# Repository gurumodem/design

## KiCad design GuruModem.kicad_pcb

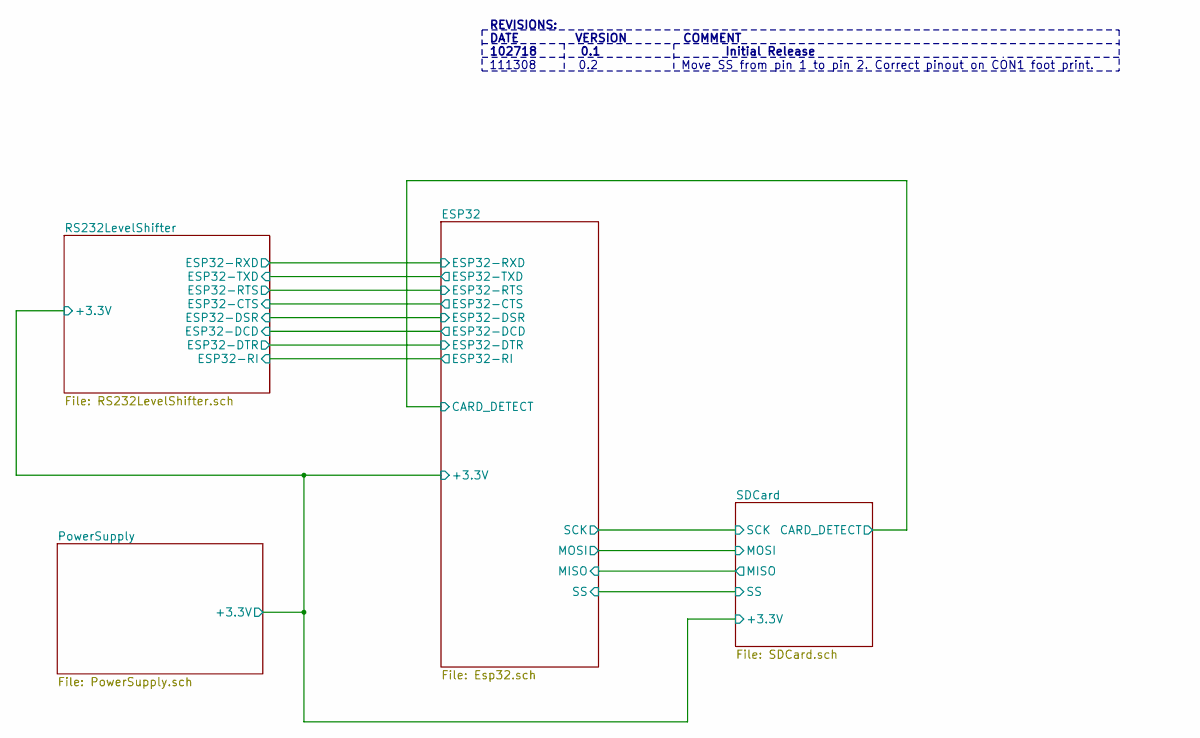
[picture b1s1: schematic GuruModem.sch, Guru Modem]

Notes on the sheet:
REVISIONS: DATE VERSION COMMENT 102718 0.1 Initial Release
111308
0.2
Move SS from pin 1 to pin 2. Correct pinout on CON1 foot print.

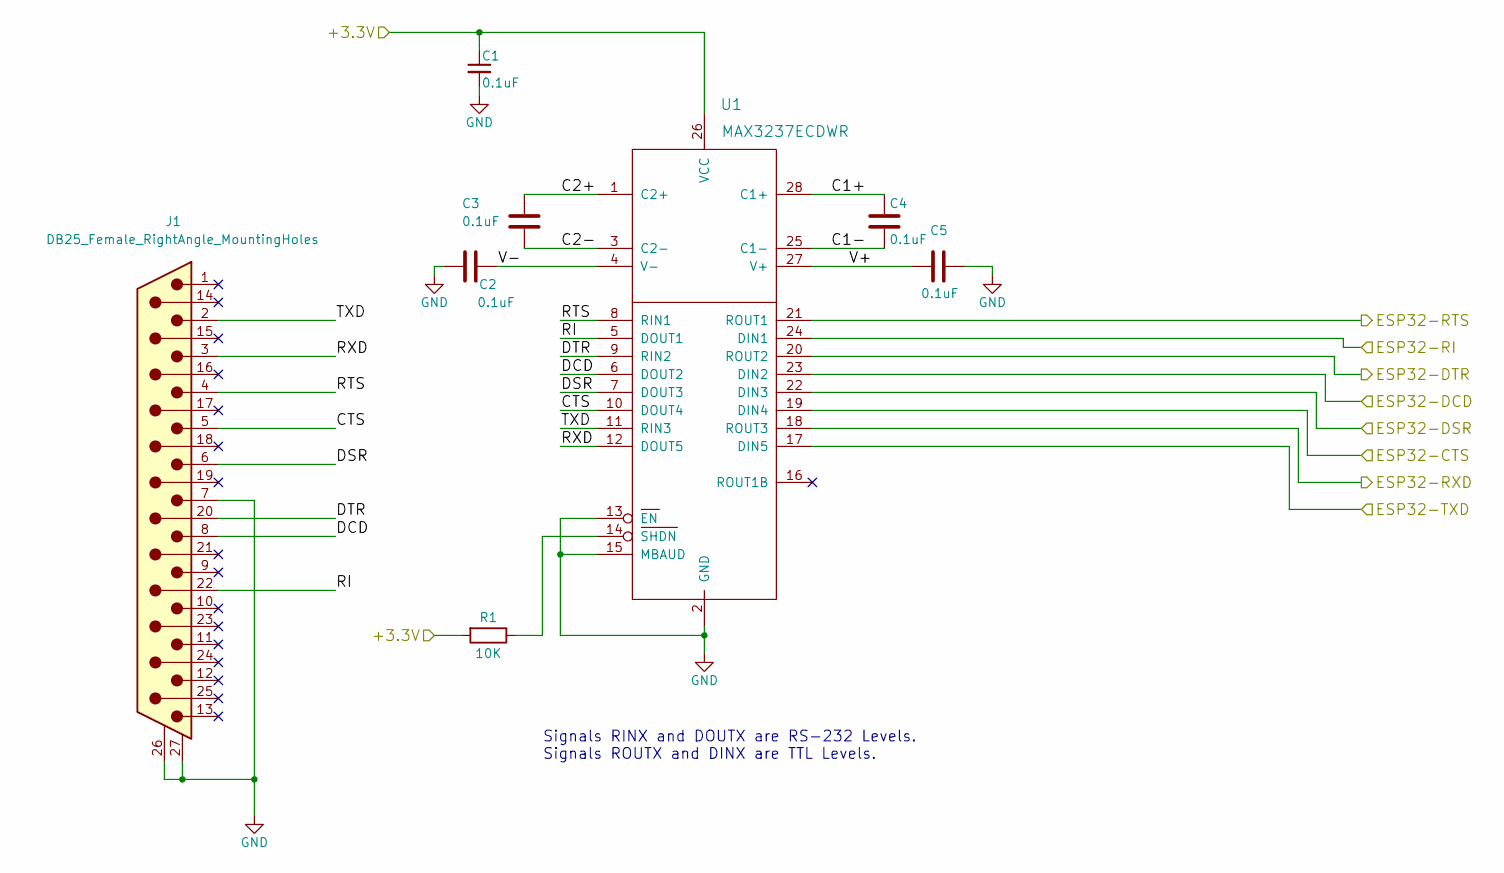
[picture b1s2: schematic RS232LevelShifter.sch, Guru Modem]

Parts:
C1, C2, C3, C4, C5: 0.1uF; C_0805
J1: DB25_Female_RightAngle_MountingHoles; DSUB-25_Female_RightAngle_MountingHoles
R1: 10K; R_0805
U1: MAX3237ECDWR; SOIC-28DW

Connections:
+3V3: C1.1, R1.2, U1.26 (VCC); also elsewhere on the board
/ESP32/ESP32-CTS: U1.19 (DIN4); also elsewhere on the board
/ESP32/ESP32-DCD: U1.23 (DIN2); also elsewhere on the board
/ESP32/ESP32-DSR: U1.22 (DIN3); also elsewhere on the board
/ESP32/ESP32-DTR: U1.20 (ROUT2); also elsewhere on the board
/ESP32/ESP32-RI: U1.24 (DIN1); also elsewhere on the board
/ESP32/ESP32-RTS: U1.21 (ROUT1); also elsewhere on the board
/ESP32/ESP32-RXD: U1.18 (ROUT3); also elsewhere on the board
/ESP32/ESP32-TXD: U1.17 (DIN5); also elsewhere on the board
/RS232LevelShifter/C1+: C4.1, U1.28 (C1+)
/RS232LevelShifter/C1-: C4.2, U1.25 (C1-)
/RS232LevelShifter/C2+: C3.1, U1.1 (C2+)
/RS232LevelShifter/C2-: C3.2, U1.3 (C2-)
/RS232LevelShifter/CTS: J1.5, U1.10 (DOUT4)
/RS232LevelShifter/DCD: J1.8, U1.6 (DOUT2)
/RS232LevelShifter/DSR: J1.6, U1.7 (DOUT3)
/RS232LevelShifter/DTR: J1.20, U1.9 (RIN2)
/RS232LevelShifter/RI: J1.22, U1.5 (DOUT1)
/RS232LevelShifter/RTS: J1.4, U1.8 (RIN1)
/RS232LevelShifter/RXD: J1.3, U1.12 (DOUT5)
/RS232LevelShifter/TXD: J1.2, U1.11 (RIN3)
/RS232LevelShifter/V+: C5.2, U1.27 (V+)
/RS232LevelShifter/V-: C2.2, U1.4 (V-)
GND: C1.2, C2.1, C5.1, J1.7, J1.26 (GND), J1.27 (GND), U1.2 (GND), U1.13 (EN), U1.15 (MBAUD); also elsewhere on the board
unnamed: R1.1, U1.14 (SHDN)

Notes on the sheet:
Signals RINX and DOUTX are RS-232 Levels. Signals ROUTX and DINX are TTL Levels.

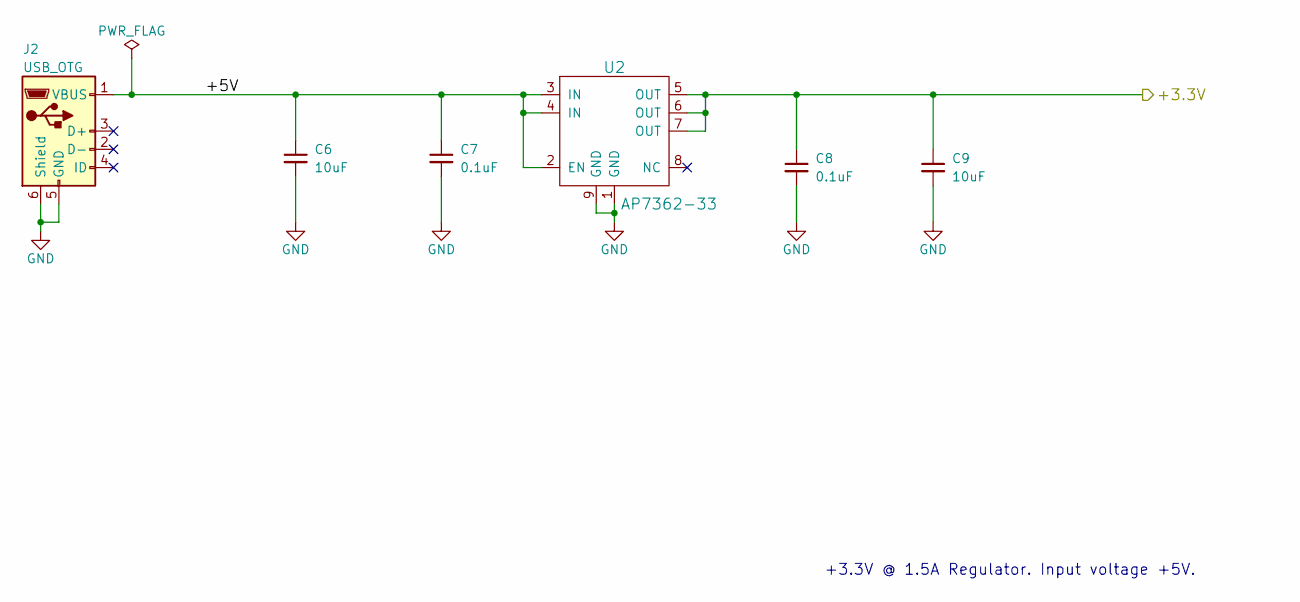
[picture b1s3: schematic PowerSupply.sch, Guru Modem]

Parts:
C6, C9: 10uF; C_0805
C7, C8: 0.1uF; C_0805
J2: USB_OTG; CUI_Micro_USB_SMT_UJ2-MIBH2-4-SMT
U2: AP7362-33; SO-8EP

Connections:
+3V3: C8.1, C9.1, U2.5 (OUT), U2.6 (OUT), U2.7 (OUT); also elsewhere on the board
/PowerSupply/+5V: C6.1, C7.1, J2.1 (VBUS), U2.2 (EN), U2.3 (IN), U2.4 (IN)
GND: C6.2, C7.2, C8.2, C9.2, J2.5 (GND), J2.6 (Shield), U2.1 (GND), U2.9 (GND); also elsewhere on the board

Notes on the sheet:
+3.3V @ 1.5A Regulator. Input voltage +5V.

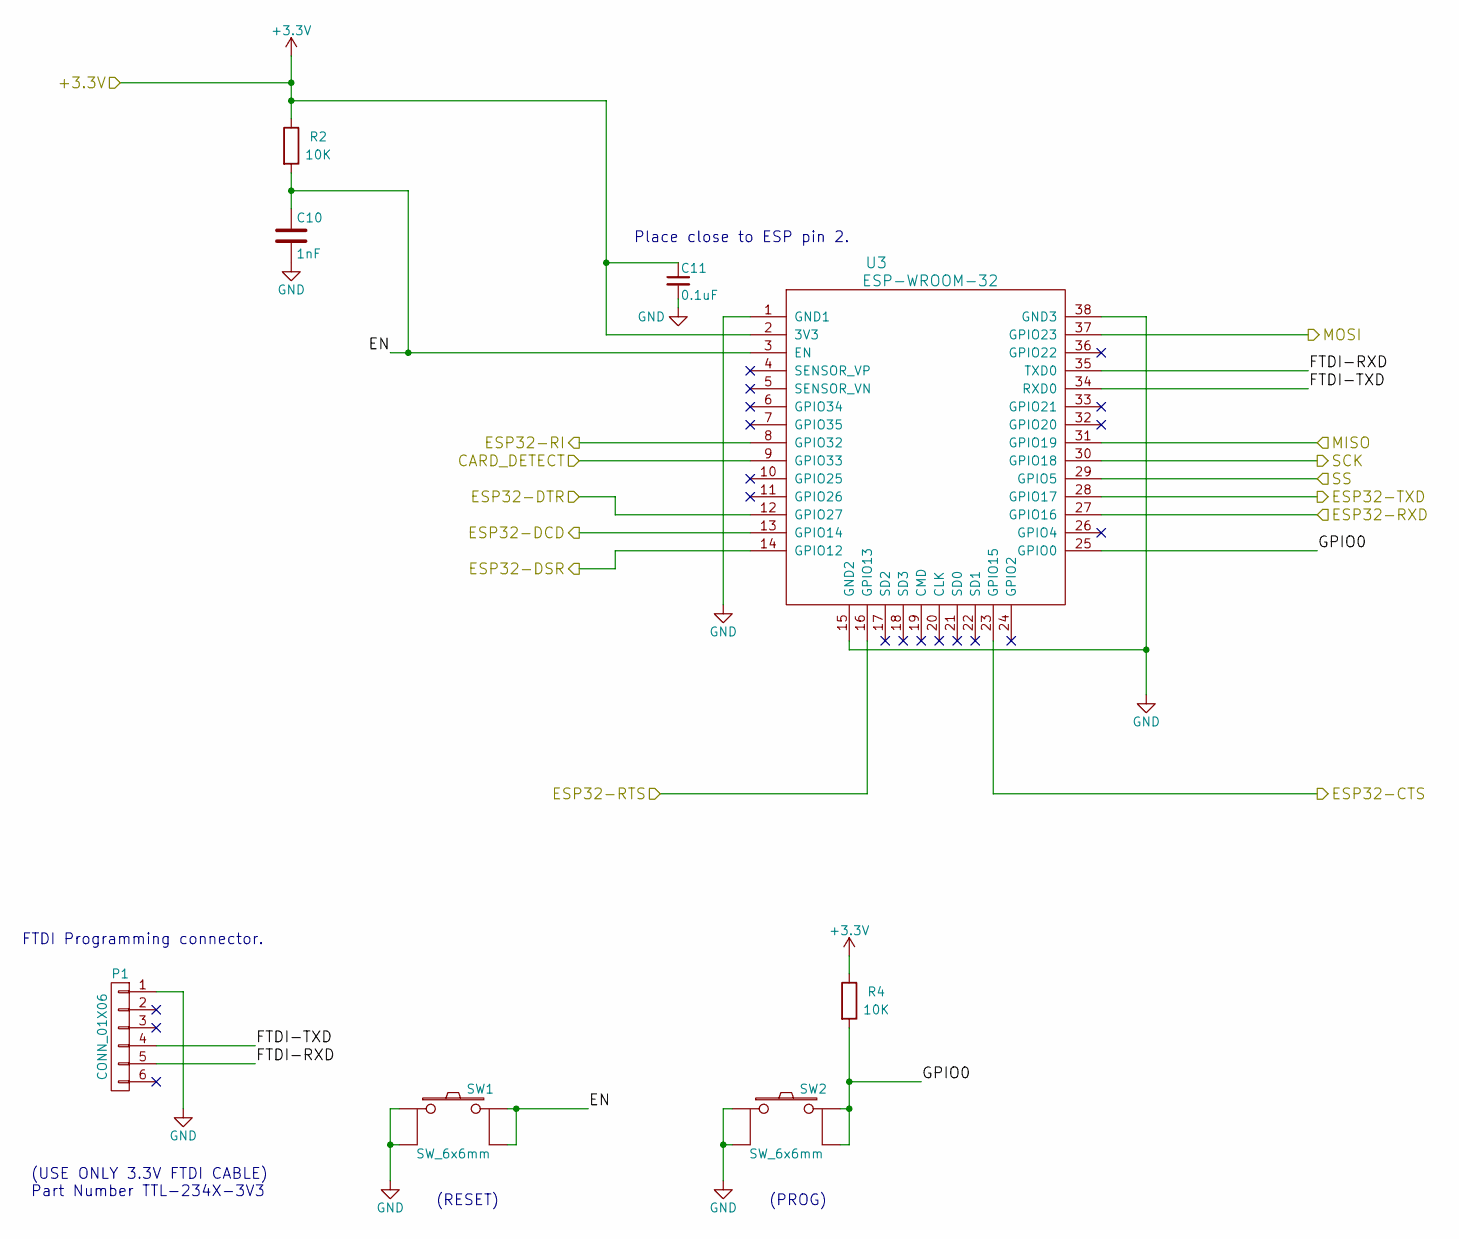
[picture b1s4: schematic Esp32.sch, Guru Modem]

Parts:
C10: 1nF; C_0805
C11: 0.1uF; C_0805
P1: CONN_01X06; HDR_6-PIN_STAGGERD
R2, R4: 10K; R_0805
SW1, SW2: SW_6x6mm; Micro-PUSHBUTTON
U3: ESP-WROOM-32

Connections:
+3V3: C11.1, R2.1, R4.1, U3.2 (3V3); also elsewhere on the board
/ESP32/CARD_DETECT: U3.9 (GPIO33); also elsewhere on the board
/ESP32/EN: C10.1, R2.2, SW1.3, SW1.4, U3.3 (EN)
/ESP32/ESP32-CTS: U3.23 (GPIO15); also elsewhere on the board
/ESP32/ESP32-DCD: U3.13 (GPIO14); also elsewhere on the board
/ESP32/ESP32-DSR: U3.14 (GPIO12); also elsewhere on the board
/ESP32/ESP32-DTR: U3.12 (GPIO27); also elsewhere on the board
/ESP32/ESP32-RI: U3.8 (GPIO32); also elsewhere on the board
/ESP32/ESP32-RTS: U3.16 (GPIO13); also elsewhere on the board
/ESP32/ESP32-RXD: U3.27 (GPIO16); also elsewhere on the board
/ESP32/ESP32-TXD: U3.28 (GPIO17); also elsewhere on the board
/ESP32/FTDI-RXD: P1.5, U3.35 (TXD0)
/ESP32/FTDI-TXD: P1.4, U3.34 (RXD0)
/ESP32/GPIO0: R4.2, SW2.3, SW2.4, U3.25 (GPIO0)
/ESP32/MISO: U3.31 (GPIO19); also elsewhere on the board
/ESP32/MOSI: U3.37 (GPIO23); also elsewhere on the board
/ESP32/SCK: U3.30 (GPIO18); also elsewhere on the board
/ESP32/SS: U3.29 (GPIO5); also elsewhere on the board
GND: C10.2, C11.2, P1.1, SW1.1, SW1.2, SW2.1, SW2.2, U3.1 (GND1), U3.15 (GND2), U3.38 (GND3), U3.39 (GND); also elsewhere on the board

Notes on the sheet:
Place close to ESP pin 2.
FTDI Programming connector.
(RESET)
(USE ONLY 3.3V FTDI CABLE) Part Number TTL-234X-3V3
(PROG)

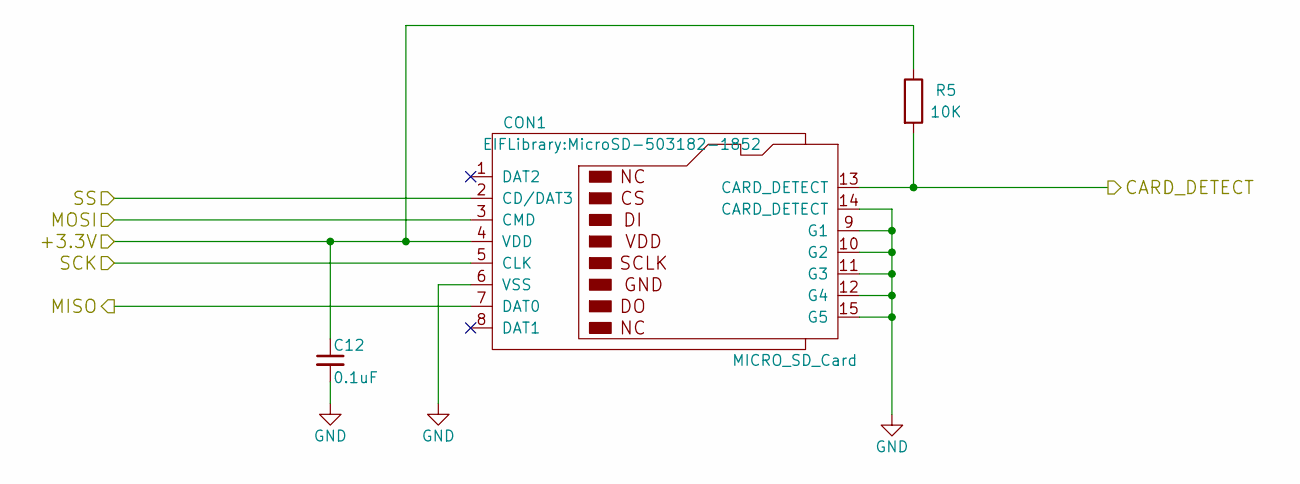
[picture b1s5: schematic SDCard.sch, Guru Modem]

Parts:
C12: 0.1uF; C_0805
CON1: MICRO_SD_Card; MicroSD-503182-1852
R5: 10K; R_0805

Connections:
+3V3: C12.1, CON1.4 (VDD), R5.1; also elsewhere on the board
/ESP32/CARD_DETECT: CON1.13 (CARD_DETECT), R5.2; also elsewhere on the board
/ESP32/MISO: CON1.7 (DAT0); also elsewhere on the board
/ESP32/MOSI: CON1.3 (CMD); also elsewhere on the board
/ESP32/SCK: CON1.5 (CLK); also elsewhere on the board
/ESP32/SS: CON1.2 (CD/DAT3); also elsewhere on the board
GND: C12.2, CON1.6 (VSS), CON1.9 (G1), CON1.10 (G2), CON1.11 (G3), CON1.12 (G4), CON1.14 (CARD_DETECT), CON1.15 (G5); also elsewhere on the board

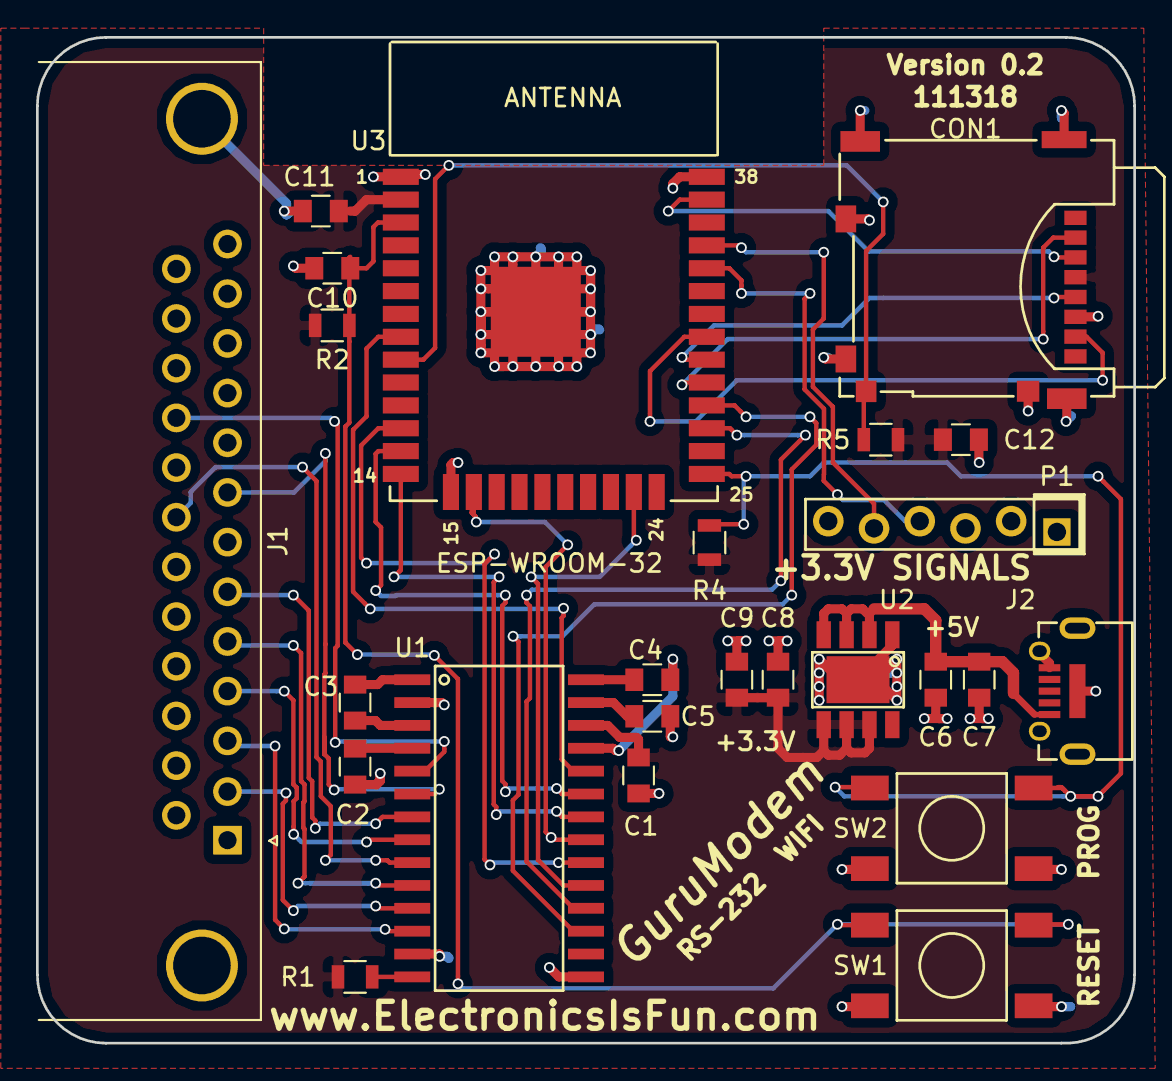
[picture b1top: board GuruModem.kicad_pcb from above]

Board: 2 copper layers, 61.0 x 55.9 mm, 25 parts (0 on the bottom side), 35 nets.

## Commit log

2019-03-13 Initial upload
    GuruModem version 0.2 Design Files
